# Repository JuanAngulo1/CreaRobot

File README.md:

# Sesame Robot — Build Guide (Custom Variant)

> Basado en el proyecto original [dorianborian/sesame-robot](https://github.com/dorianborian/sesame-robot) con modificaciones propias: alimentación por batería LiPo 2S con regulador LM2596, PCB personalizada y soporte para pantalla OLED con JST.

---

## Tabla de contenido

1. [Visión general](#1-visión-general)
2. [BOM — Lista de materiales](#2-bom--lista-de-materiales)
3. [Impresión 3D](#3-impresión-3d)
4. [Fase 1 — Electrónica: soldadura de la PCB](#4-fase-1--electrónica-soldadura-de-la-pcb)
5. [Fase 2 — Sistema de alimentación](#5-fase-2--sistema-de-alimentación)
6. [Fase 3 — Ensamblaje mecánico](#6-fase-3--ensamblaje-mecánico)
7. [Fase 4 — Montaje de la electrónica en el cuerpo](#7-fase-4--montaje-de-la-electrónica-en-el-cuerpo)
8. [Fase 5 — Calibración de servos](#8-fase-5--calibración-de-servos)
9. [Fase 6 — Firmware](#9-fase-6--firmware)

---

## 1. Visión general

El robot es un cuadrúpedo miniatura con 8 servos (2 por pata), controlado por un ESP32-S2 Mini (Lolin). La variante descrita aquí usa:

- Batería LiPo 2S (2× celda 14500 en battery holder 2S) → regulador buck LM2596 → 5 V para toda la electrónica.
- PCB de distribución personalizada con conectores JST XH 2.54 mm.
- Pantalla OLED SSD1306 0.96″ conectada por JST de 4 pines.
- Switch de encendido integrado en el top cover.

---

## 2. BOM — Lista de materiales

### Electrónica

| Componente | Especificación | Cant. |
|---|---|---|
| Microcontrolador | Lolin ESP32-S2 Mini | 1 |
| Servos | Tower Pro MG90S (o equivalente micro servo) | 8 |
| Pantalla OLED | SSD1306 0.96″, I2C | 1 |
| Regulador buck | LM2596 (módulo ajustable) | 1 |
| Batería | LiPo 14500 3.7 V × 2 (en battery holder 2S) | 2 |
| Switch | Rocker switch, enclave, 2 pines | 1 |

### Conectores y pasivos (para la PCB)

| Componente | Especificación | Cant. |
|---|---|---|
| Regleta hembra 2.54 mm | Para montar el ESP32-S2 Mini | 2 (según pinout) |
| Regleta macho 2.54 mm | Para señal de cada servo (S/VCC/GND por canal) | 8 × 3 pines |
| JST XH 2.54 mm 2 pines | Entrada de 5 V desde el buck | 1 |
| JST XH 2.54 mm 4 pines | Pantalla OLED (VCC, GND, SDA, SCL) | 1 |
| Cable 30 AWG | Señal | c/n |
| Cable 22 AWG | Potencia (VCC/GND servos y alimentación) | c/n |

### Hardware mecánico

| Componente | Especificación | Cant. |
|---|---|---|
| Tornillos autoroscantes | M2 × 5 mm | 10 |
| Tornillos métricos | M3 × 5 mm | 4 (regulador en techo) |
| Tuercas M3 | Para el regulador | 4 |

### Partes impresas en 3D

| Pieza | Cantidad |
|---|---|
| Marco interno (Internal Frame) | 1 |
| Top Cover | 1 |
| Bottom Cover | 1 |
| Joint L1, L2, L3, L4 | 1 c/u |
| Joint R1, R2, R3, R4 | 1 c/u |

---

## 3. Impresión 3D

Imprime todas las piezas antes de empezar el ensamblaje.

- **Material:** PLA (recomendado)
- **Relleno:** 30–40%
- **Capa:** 0.2 mm
- **Soportes:** Revisar el printing guide del repo original para orientaciones específicas del top cover

El set completo son **11 piezas impresas**: marco interno, top cover, bottom cover, y 8 joints (L1–L4, R1–R4).

![Componentes del robot]    
*Vista general de todos los componentes mecánicos e impresos*

---

## 4. Fase 1 — Electrónica: soldadura de la PCB

> Hazlo antes de tocar el ensamblaje mecánico. Con la PCB lista el cableado interno es mucho más limpio.

### 4.1 Montar el ESP32-S2 Mini

Solda dos **regletas hembra de 2.54 mm** en la PCB para que el ESP32-S2 Mini quede en zócalo (desmontable). El ESP32-S2 Mini requiere un reset manual para flashear (no tiene DTR/RTS automático), así que dejarlo desmontable facilita la vida.

### 4.2 Regletas para servos

Por cada uno de los 8 servos, solda una **regleta macho de 3 pines** (Señal / VCC / GND). Etiquétalas del 0 al 7 según el mapa de pines del firmware. Los servos L1–L4 y R1–R4 conectan aquí.

### 4.3 Conector de alimentación (entrada 5 V)

Solda un **JST XH 2.54 mm de 2 pines** para recibir los 5 V desde la salida del regulador LM2596. Esta es la única fuente de alimentación de toda la PCB (ESP32 + servos).

### 4.4 Conector de pantalla OLED

Solda un **JST XH 2.54 mm de 4 pines** con el siguiente orden:

```
Pin 1 → VCC (3.3 V o 5 V según la pantalla)
Pin 2 → GND
Pin 3 → SDA  (GPIO 33 en el S2 Mini por defecto)
Pin 4 → SCL  (GPIO 35 en el S2 Mini por defecto)
```

> Verificar el pinout exacto en el archivo de firmware antes de soldar.

### 4.5 Checklist de PCB

- [ ] ESP32-S2 Mini en zócalo, sin cortocircuitos visibles
- [ ] 8 regletas de servo soldadas y etiquetadas (0–7)
- [ ] JST 2 pines de alimentación
- [ ] JST 4 pines de OLED con orden VCC/GND/SDA/SCL correcto

---

## 5. Fase 2 — Sistema de alimentación

### 5.1 Batería

Usa **2 celdas 14500** (3.7 V cada una) en un **battery holder 2S**. Con ambas en serie obtienes ~7.4 V nominal (8.4 V cargadas). El holder va en la cavidad del Bottom Cover.

### 5.2 Regulador LM2596

El LM2596 convierte los 7.4–8.4 V de la batería a **5 V estables** para todo el sistema.

**Procedimiento de ajuste (trimear) antes de instalar:**

1. Conecta la batería (sin carga) al input del LM2596.
2. Con un multímetro en la salida, ajusta el **potenciómetro** del módulo hasta leer exactamente **5.0 V**.
3. Verifica con una carga leve (ej. una resistencia de 10 Ω) que la tensión se mantiene estable.

**Instalación:** El regulador se monta en el interior del top cover, pegado al techo, sujeto con **4 tornillos M3 × 5 mm** + tuercas. Deja espacio para que el potenciómetro quede accesible si necesitas reajustar.

### 5.3 Switch de encendido

El rocker switch se integra en el top cover. Se corta el positivo de la batería y se interrumpe con el switch — cuando está en OFF desconecta completamente el pack.

*El switch encaja en la ranura del top cover presionando desde arriba*

---

## 6. Fase 3 — Ensamblaje mecánico

### 6.1 Montaje de servos en joints L3, L4, R3, R4 (patas traseras/delanteras, motor lateral)

Cada joint lateral (L3/R3 = muslo, L4/R4 = tibia) recibe un servo con el **engranaje apuntando hacia arriba** desde la perspectiva de la pata.

*Check verde = orientación correcta del servo en cada joint*

Fijación: **2× M2 × 5 mm autoroscantes** por servo (los orificios de montaje del servo encajan en el slot del joint).

### 6.2 Montaje de servos en joints L1, L2, R1, R2 (cadera)

Los joints de cadera son la articulación entre el cuerpo y la pata. Se montan en pares (L1+L2 lado izquierdo, R1+R2 lado derecho).

*Los cuatro joints de cadera, verificados con check verde*

> ⚠️ En este punto **NO montes todavía los servos** en los joints de cadera. Primero van los joints al frame, después los servos. Ver imagen de referencia:

### 6.3 Montaje en el marco interno

Los servos de cadera (motores 1–4, que corresponden a L1/L2/R1/R2) se insertan en el internal frame desde abajo. El servo desliza hacia arriba dentro de su slot, con las pestañas del servo encajando en las guías del frame.

*4 servos fijados al frame con M2 × 5 mm self-tapping, check verde en cada esquina*

### 6.4 Verificación de orientación antes de continuar

Con los joints y el frame armados, revisa que la geometría de patas corresponda al diagrama de ángulos. **Todos los servos deben estar a 90° para el ensamblaje inicial** (posición neutra):

*Mapa de ángulos objetivo por servo. "Vertical angles represent straight down"*

---

## 7. Fase 4 — Montaje de la electrónica en el cuerpo

### 7.1 PCB en el internal frame

La PCB de distribución va en el internal frame. Alinea los orificios de montaje y fija con tornillos M2.

### 7.2 Regulador en el top cover

El LM2596 va en el interior del top cover, pegado al techo. Sujétalo con los **4 M3 × 5 mm** mencionados en la Fase 2.

### 7.3 Pantalla OLED

La pantalla tiene un soporte impreso que la fija en la ranura frontal del top cover. Conecta el cable JST de 4 pines que va de la pantalla a la PCB.

### 7.4 Batería en el bottom cover

El battery holder 2S va en la cavidad del bottom cover. El cable positivo pasa por el switch antes de llegar al input del LM2596.

---

## 8. Fase 5 — Calibración de servos

Antes de poner los brazos de servo (servo horns) en su posición definitiva, todos los servos deben estar en **90°**.

1. Flashea `sesame-motor-tester.ino` (debugging firmware) al ESP32-S2 Mini via Arduino IDE.
2. Abre el Serial Monitor a 115200 baud.
3. Sigue el menú para mover cada servo individualmente a 90°.
4. Anota el offset de cada canal si el servo no queda perfectamente centrado.
5. Fija el servo horn con los servos ya en 90° antes de cerrar las articulaciones.

> Los offsets se ajustan en los parámetros de configuración del firmware principal.

---

## 9. Fase 6 — Firmware

### 9.1 Requisitos

- Arduino IDE con soporte para ESP32 (board manager: `https://raw.githubusercontent.com/espressif/arduino-esp32/gh-pages/package_esp32_index.json`)
- Board seleccionada: **LOLIN S2 Mini**

### 9.2 Flash del firmware principal

```bash
# Clonar el repo
git clone https://github.com/dorianborian/sesame-robot.git
cd sesame-robot/firmware
```

Abre `sesame-firmware-main.ino` en Arduino IDE y carga al ESP32-S2 Mini.

> ⚠️ El S2 Mini **no tiene DTR/RTS automático**. Para entrar en modo bootloader: mantén presionado **BOOT**, presiona y suelta **RST**, luego suelta **BOOT**. Después de flashear, presiona RST una vez para arrancar.

### 9.3 Control

Una vez encendido, el ESP32 levanta un **Access Point WiFi**. Conéctate desde tu teléfono a la red del robot y accede a la IP del AP (normalmente `192.168.4.1`) para ver el control web.

## Checklist final de ensamblaje

- [ ] PCB soldada y revisada sin cortocircuitos
- [ ] Regulador LM2596 trimeado a 5.0 V
- [ ] Switch probado (corta el positivo correctamente)
- [ ] Todos los servos centrados a 90° con `sesame-motor-tester`
- [ ] Joints y servos orientados según el diagrama de ángulos
- [ ] OLED conectada y mostrando algo al encender
- [ ] Firmware principal cargado, WiFi AP activo
- [ ] Batería colocada en el bottom cover, robot cierra correctamente

---

*Basado en [dorianborian/sesame-robot](https://github.com/dorianborian/sesame-robot). Variante con LiPo 2S + LM2596 + PCB de distribución personalizada.*

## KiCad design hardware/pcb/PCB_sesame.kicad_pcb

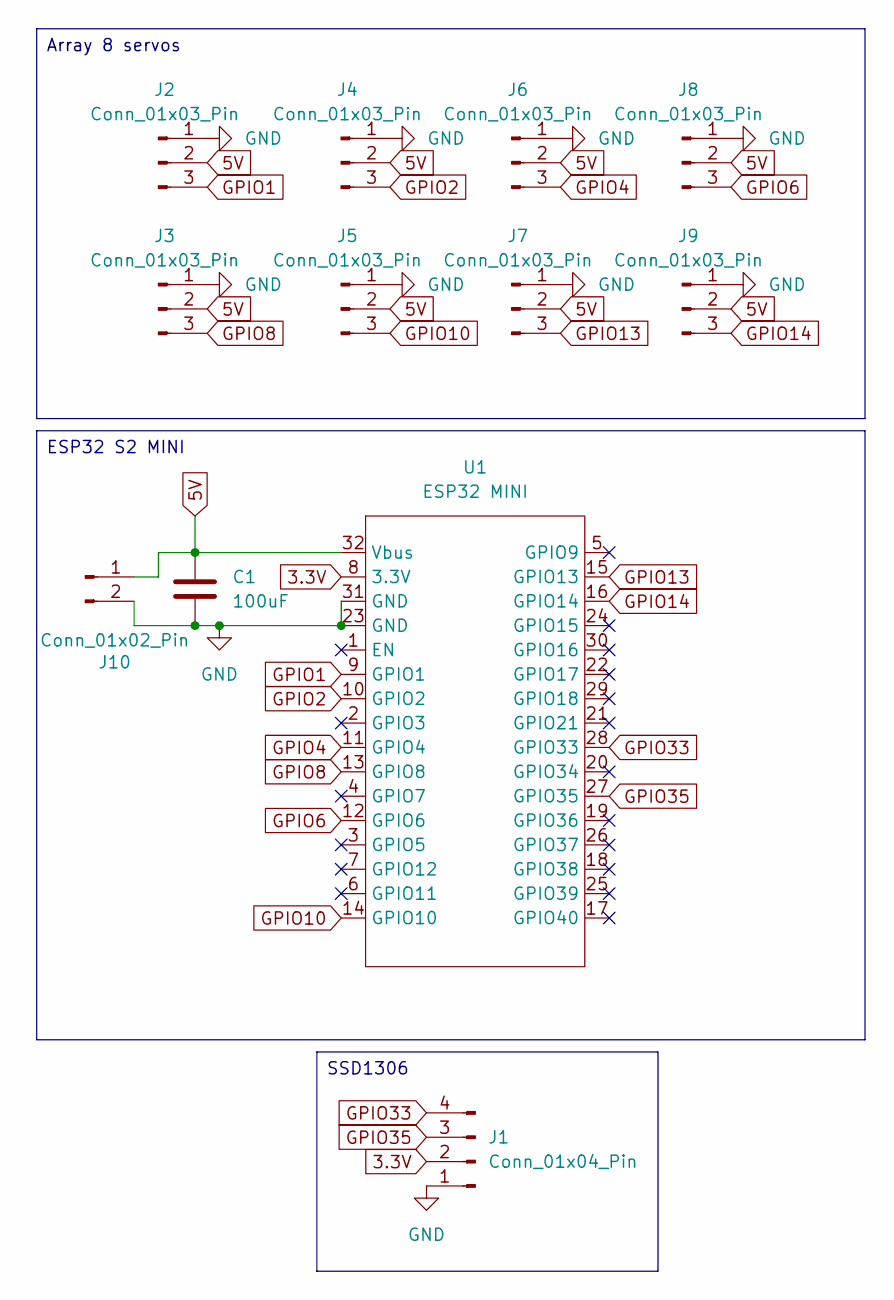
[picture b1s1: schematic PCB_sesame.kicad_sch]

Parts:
C1: 100uF; C_Radial_D6.3mm_H11.0mm_P2.50mm
J1: Conn_01x04_Pin; JST_XH_B4B-XH-A_1x04_P2.50mm_Vertical
J2, J3, J4, J5, J6, J7, J8, J9: Conn_01x03_Pin; PinHeader_1x03_P2.54mm_Vertical
J10: Conn_01x02_Pin; JST_XH_B2B-XH-A_1x02_P2.50mm_Vertical
U1: ESP32 MINI; ESP32 S2 MINI

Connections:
3.3V: J1.2, U1.8 (3.3V)
5V: C1.1, J2.2, J3.2, J4.2, J5.2, J6.2, J7.2, J8.2, J9.2, J10.1, U1.32 (Vbus)
GND: C1.2, J1.1, J2.1, J3.1, J4.1, J5.1, J6.1, J7.1, J8.1, J9.1, J10.2, U1.23 (GND), U1.31 (GND)
GPIO1: J2.3, U1.9 (GPIO1)
GPIO2: J4.3, U1.10 (GPIO2)
GPIO4: J6.3, U1.11 (GPIO4)
GPIO6: J8.3, U1.12 (GPIO6)
GPIO8: J3.3, U1.13 (GPIO8)
GPIO10: J5.3, U1.14 (GPIO10)
GPIO13: J7.3, U1.15 (GPIO13)
GPIO14: J9.3, U1.16 (GPIO14)
GPIO33: J1.4, U1.28 (GPIO33)
GPIO35: J1.3, U1.27 (GPIO35)

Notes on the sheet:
Array 8 servos
SSD1306
ESP32 S2 MINI

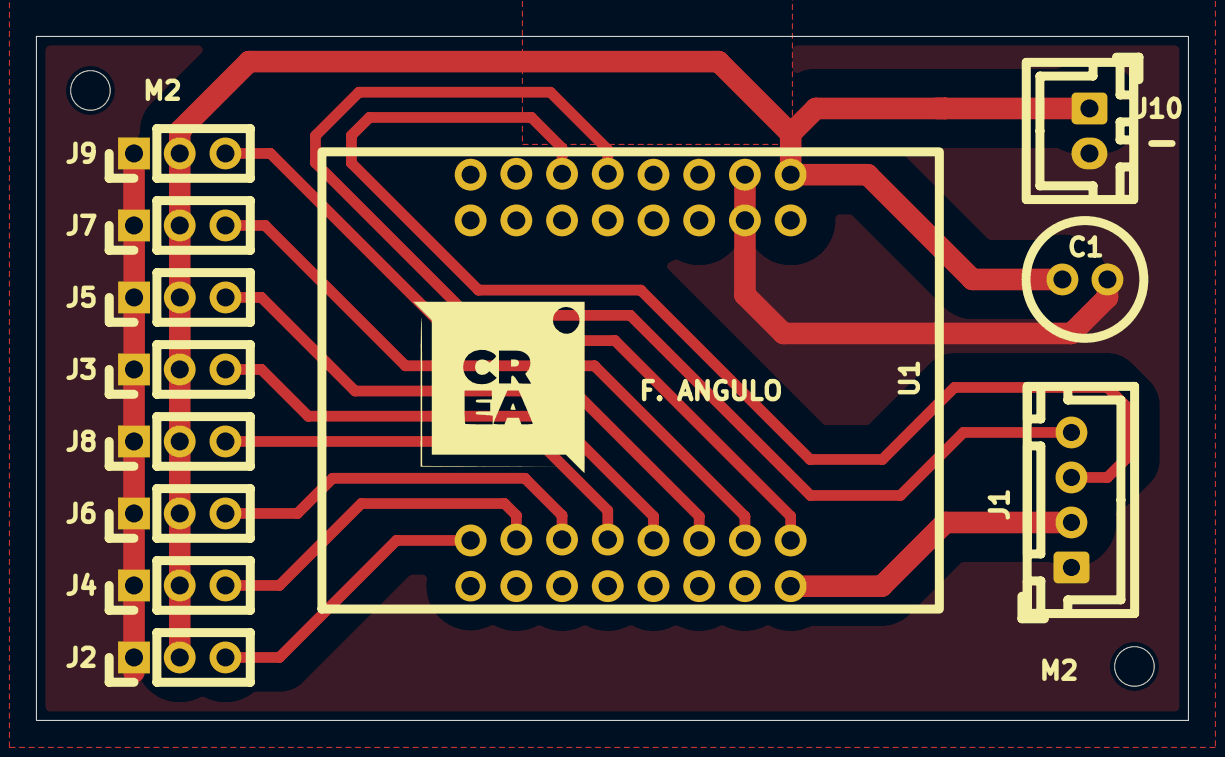
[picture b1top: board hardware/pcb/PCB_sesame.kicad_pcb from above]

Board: 2 copper layers, 64.0 x 38.0 mm, 15 parts (0 on the bottom side), 13 nets.

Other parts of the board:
.: LOGO; crea_logo
M2, M2#2: MountingHole_2.2mm_M2

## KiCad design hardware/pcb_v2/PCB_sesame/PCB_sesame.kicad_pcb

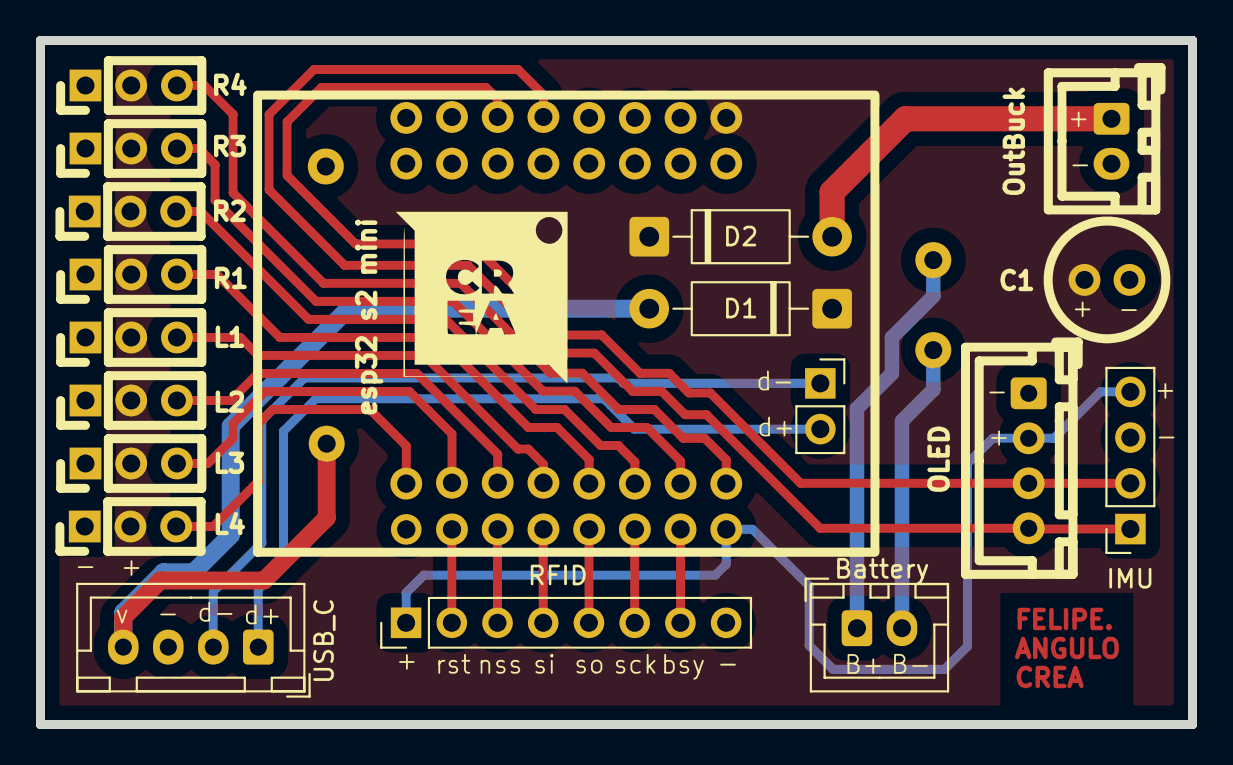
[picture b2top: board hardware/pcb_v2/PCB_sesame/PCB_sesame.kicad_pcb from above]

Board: 2 copper layers, 64.0 x 38.0 mm, 21 parts (0 on the bottom side), 25 nets.

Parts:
.: LOGO; crea_logo
Battery: Conn_01x02_Socket; JST_XH_B2B-XH-A_1x02_P2.50mm_Vertical
C1: 100uF; C_Radial_D6.3mm_H11.0mm_P2.50mm
D1, D2: 1N5819; D_DO-41_SOD81_P10.16mm_Horizontal
IMU: Conn_01x04_Pin; PinSocket_1x04_P2.54mm_Vertical
J13: Conn_01x02_Socket; PinSocket_1x02_P2.54mm_Vertical
L1, L2, L3, L4: Conn_01x03_Pin; PinHeader_1x03_P2.54mm_Vertical
OLED: Conn_01x04_Pin; JST_XH_B4B-XH-A_1x04_P2.50mm_Vertical
OutBuck: Conn_01x02_Pin; JST_XH_B2B-XH-A_1x02_P2.50mm_Vertical
R1, R2, R3, R4: Conn_01x03_Pin; PinHeader_1x03_P2.54mm_Vertical
RFID: Conn_01x08_Pin; PinHeader_1x08_P2.54mm_Vertical
U2: modulo_Carga
USB_C: Conn_01x04_Socket; JST_XH_B4B-XH-A_1x04_P2.50mm_Vertical
esp32 s2 mini: ESP32 MINI; ESP32 S2 MINI

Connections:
3.3V: IMU.4, OLED.2, RFID.1, esp32 s2 mini.8 (3.3V)
5V: C1.1, D1.1 (K), D2.1 (K), L1.2, L2.2, L3.2, L4.2, R1.2, R2.2, R3.2, R4.2, esp32 s2 mini.32 (Vbus)
BUSY: RFID.7, esp32 s2 mini.7 (GPIO12)
D+: J13.2, USB_C.1
D-: J13.1, USB_C.2
GND: C1.2, IMU.3, L1.1, L2.1, L3.1, L4.1, OLED.1, OutBuck.2, R1.1, R2.1, R3.1, R4.1, RFID.8, U2.2 (GND), USB_C.3, esp32 s2 mini.23 (GND), esp32 s2 mini.31 (GND)
GPIO1: L4.3, esp32 s2 mini.9 (GPIO1)
GPIO2: L3.3, esp32 s2 mini.10 (GPIO2)
GPIO4: L2.3, esp32 s2 mini.11 (GPIO4)
GPIO6: L1.3, esp32 s2 mini.12 (GPIO6)
GPIO8: R1.3, esp32 s2 mini.13 (GPIO8)
GPIO10: R2.3, esp32 s2 mini.14 (GPIO10)
GPIO13: R3.3, esp32 s2 mini.15 (GPIO13)
GPIO14: R4.3, esp32 s2 mini.16 (GPIO14)
GPIO33: IMU.1, OLED.4, esp32 s2 mini.28 (GPIO33)
GPIO35: IMU.2, OLED.3, esp32 s2 mini.27 (GPIO35)
MISO: RFID.5, esp32 s2 mini.5 (GPIO9)
MOSI: RFID.4, esp32 s2 mini.4 (GPIO7)
NSS: RFID.3, esp32 s2 mini.3 (GPIO5)
unnamed: Battery.1, U2.4 (B+)
unnamed: Battery.2, U2.3 (B-)
unnamed: D2.2 (A), OutBuck.1
RST: RFID.2, esp32 s2 mini.2 (GPIO3)
SCK: RFID.6, esp32 s2 mini.6 (GPIO11)
VBUS: D1.2 (A), U2.1 (VBUS), USB_C.4

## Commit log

2026-06-02 Add new file a in hardware/pcb_v2 directory
2026-06-02 Crear carpeta pcb_v2 y agregar archivos
2026-06-02 Mover pcb_v2 dentro de hardware
